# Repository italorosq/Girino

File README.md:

# Girino

Plataforma didática do **LaRA** (Laboratório de Robótica e Automação) para ensino de controle de motores DC. Integra microcontrolador com Wi-Fi, driver de potência L298N e encoder em uma bancada compacta para introdução prática à leitura de sensores, modulação PWM, controle PID e sintonia em malha fechada.

A interface web é embarcada no próprio ESP8266: o aluno conecta na rede do Girino e controla a bancada pelo navegador do celular ou notebook — sem instalar MATLAB, Python ou qualquer software, e sem depender de internet.

## Status do Projeto

| Componente | Status |
|---|---|
| Estrutura do repositório | ✅ Criada |
| Firmware (ESP8266) | ✅ Funcional — PID de velocidade/posição e auto-tune validados em bancada |
| Hardware (PCB — KiCad) | ✅ Projeto KiCad + arquivos de fabricação |
| Mecânico (caixa 3D) | ✅ Modelos STEP (caixa e tampa) |
| Documentação | ✅ |
| Exemplos didáticos | ✅ 5 exemplos |

## Funcionalidades

- **Access Point próprio** (`GIRINO_AP`, `http://192.168.4.1`) — funciona sem roteador e sem internet
- Controle PWM de motor DC via ESP8266 (4 kHz, 8 bits)
- Leitura de encoder incremental (LPD3806-600BM — 600 PPR)
- **Controle PID de velocidade (RPM) e de posição (graus)** em malha fechada
- **Auto-sintonia por relay feedback** (Åström-Hägglund) para velocidade e posição
- **Comparação de métodos de sintonia**: Ziegler-Nichols, Tyreus-Luyben e Cohen-Coon
- Interface web em 3 abas (Velocidade / Posição / Manual), com gráfico de resposta (Chart.js local) e exportação CSV
- **Console serial de comandos** — opera a bancada sem Wi-Fi
- **Auto-calibração do sentido** motor/encoder (fiação invertida corrigida em software)
- Atualização de firmware via OTA (ElegantOTA)
- Design compacto para bancada de laboratório

## Componentes de Hardware

| Componente | Descrição |
|---|---|
| ESP8266 WROOM | Microcontrolador com Wi-Fi (Access Point) |
| LPD3806-600BM | Encoder incremental, 600 pulsos/revolução (saída coletor aberto — pull-up 4,7k para 3,3 V) |
| L298N | Driver de potência do motor DC (ponte H) |
| Motor DC | Motor da bancada |
| Módulo conversão de tensão | Regulador de tensão para alimentação do circuito |

Ligações, pull-ups e montagem passo a passo em [`docs/hardware-assembly.md`](docs/hardware-assembly.md).

## Bancada Medida

| Grandeza | Valor |
|---|---|
| Zona morta do motor | ~60% de duty (abaixo disso o eixo não gira) |
| Região confiável | 70% de duty ≈ 400 RPM |
| Velocidade máxima | 100% ≈ 1950 RPM |
| Precisão de posição | ±2° (o erro residual de ~1–2° é folga mecânica da correia, não do PID) |

## Estrutura do Repositório

```
Girino/
├── firmware/          # Firmware ESP8266 (PlatformIO) + interface web (LittleFS em data/)
├── hardware/          # PCB KiCad, arquivos de fabricação (gerber/NC) e modelos 3D
├── mechanical/        # Peças 3D (em preparação)
├── docs/              # Documentação, pesquisa e infográfico
├── examples/          # Exemplos didáticos passo a passo
├── gallery/           # Fotos e renders do projeto
└── .github/           # Templates e CI/CD
```

## Início Rápido

Veja o guia completo em [`docs/getting-started.md`](docs/getting-started.md).

### Pré-requisitos

- [PlatformIO](https://platformio.org/) (extensão VSCode recomendada)
- Cabo USB para a gravação inicial do ESP8266
- Componentes e montagem: ver [`docs/hardware-assembly.md`](docs/hardware-assembly.md)

### Compilar e Gravar

```bash
cd firmware

# 1. Configurar o Access Point do Girino (SSID, senha e senha do OTA)
cp .env.example .env

# 2. Primeira gravação via USB: firmware + interface web (LittleFS)
pio run -t upload
pio run -t uploadfs

# 3. Conectar no Wi-Fi GIRINO_AP e abrir http://192.168.4.1

# 4. Atualizações seguintes via OTA (PC conectado ao GIRINO_AP)
pio run -t upload --upload-port 192.168.4.1
```

> **Importante:** `pio run -t upload` grava apenas o firmware. A interface web
> vive no LittleFS e é gravada com `pio run -t uploadfs` — obrigatório na
> primeira gravação e sempre que alterar arquivos de `firmware/data/`.

## Documentação

- [Guia de Início Rápido](docs/getting-started.md)
- [Montagem do Hardware](docs/hardware-assembly.md)
- [Guia do Firmware](firmware/README.md) — API REST, pinagem e console serial
- [Atualização OTA](docs/ota-update-guide.md)
- [Análise Comparativa](docs/analise-comparativa.md) — trabalhos relacionados e gap de pesquisa
- [Referências de Pesquisa](docs/referencias-pesquisa.md)
- [Plano PID](docs/plano-pid.md) — métodos de sintonia e arquitetura
- [Resumo UERJ Sem Muros](docs/resumo-uerj-sem-muros.md) — divulgação do projeto

## Exemplos Didáticos

| # | Exemplo | Descrição |
|---|---|---|
| 01 | [Controle Básico de Motor](examples/01-basic-motor-control/) | PWM para controlar velocidade do motor |
| 02 | [Leitura de Encoder](examples/02-encoder-reading/) | Ler pulsos e calcular velocidade |
| 03 | [Controle PID](examples/03-pid-speed-control/) | Malha fechada de velocidade |
| 04 | [OTA Web Update](examples/04-ota-web-update/) | Atualizar firmware via Wi-Fi |
| 05 | [PID Web Test](examples/05-pid-web-test/) | Teste prático de PID com painel web e gráfico |

## Contribuindo

Contribuições são bem-vindas! Veja o guia em [`CONTRIBUTING.md`](CONTRIBUTING.md).

## Licenças

Este projeto utiliza **tripla licença**:

| Tipo | Licença | Arquivo |
|---|---|---|
| Firmware (código) | **GPL-3.0** | [`LICENSE`](LICENSE) |
| Hardware (PCB, esquemático) | **CERN-OHL-S-2.0** | [`LICENSE`](LICENSE) |
| Documentação e imagens | **CC-BY-SA-4.0** | [`LICENSE`](LICENSE) |

## Equipe

Desenvolvido no **LaRA — Laboratório de Robótica e Automação** (UERJ).

## Agradecimentos

- Comunidade open-source ESP8266
- [ElegantOTA](https://github.com/ayushsharma82/ElegantOTA)
- [PlatformIO](https://platformio.org/)

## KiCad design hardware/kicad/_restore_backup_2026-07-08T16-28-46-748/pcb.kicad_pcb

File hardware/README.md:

# Hardware — Girino

Design de PCB para a plataforma didática Girino, desenvolvido em KiCad.

## Estrutura

```
hardware/
├── kicad/          # Projeto KiCad (arquivos-fonte editáveis)
├── gerbers/        # Arquivos Gerber empacotados (.zip) para fabricação
├── bom/            # Bill of Materials (lista de materiais) em CSV
└── schematics/     # PDFs exportados do esquemático
```

## Componentes Principais

| Componente | Qtd | Descrição |
|---|---|---|
| ESP8266 WROOM | 1 | Microcontrolador Wi-Fi |
| LPD3806-600BM | 1 | Encoder incremental 600 PPR |
| Driver MOSFET | 1 | Módulo driver para motor DC |
| Regulador de tensão | 1 | Conversão de tensão para alimentação do circuito |

## Fabricação da PCB

### Gerando Gerbers no KiCad

1. Abra o projeto em `kicad/`
2. Vá em **File → Plot**
3. Selecione as camadas necessárias
4. Gere os arquivos drill
5. Empacote tudo em um `.zip` e salve em `gerbers/`

### Enviando para Fabricação

Arquivos `.zip` em `gerbers/` prontos para enviar a fabricantes como:
- [JLCPCB](https://jlcpcb.com/)
- [PCBWay](https://www.pcbway.com/)
- [Eletrrow](https://www.electrow.com/)

## Convenções

- Nomes de arquivo incluem versão: `gerbers-v1.0.zip`, `bom-v1.0.csv`
- Incluir URL do repositório no silkscreen da PCB
- Arquivos temporários de backup (`.bak`, `*-backups/`) são ignorados pelo git

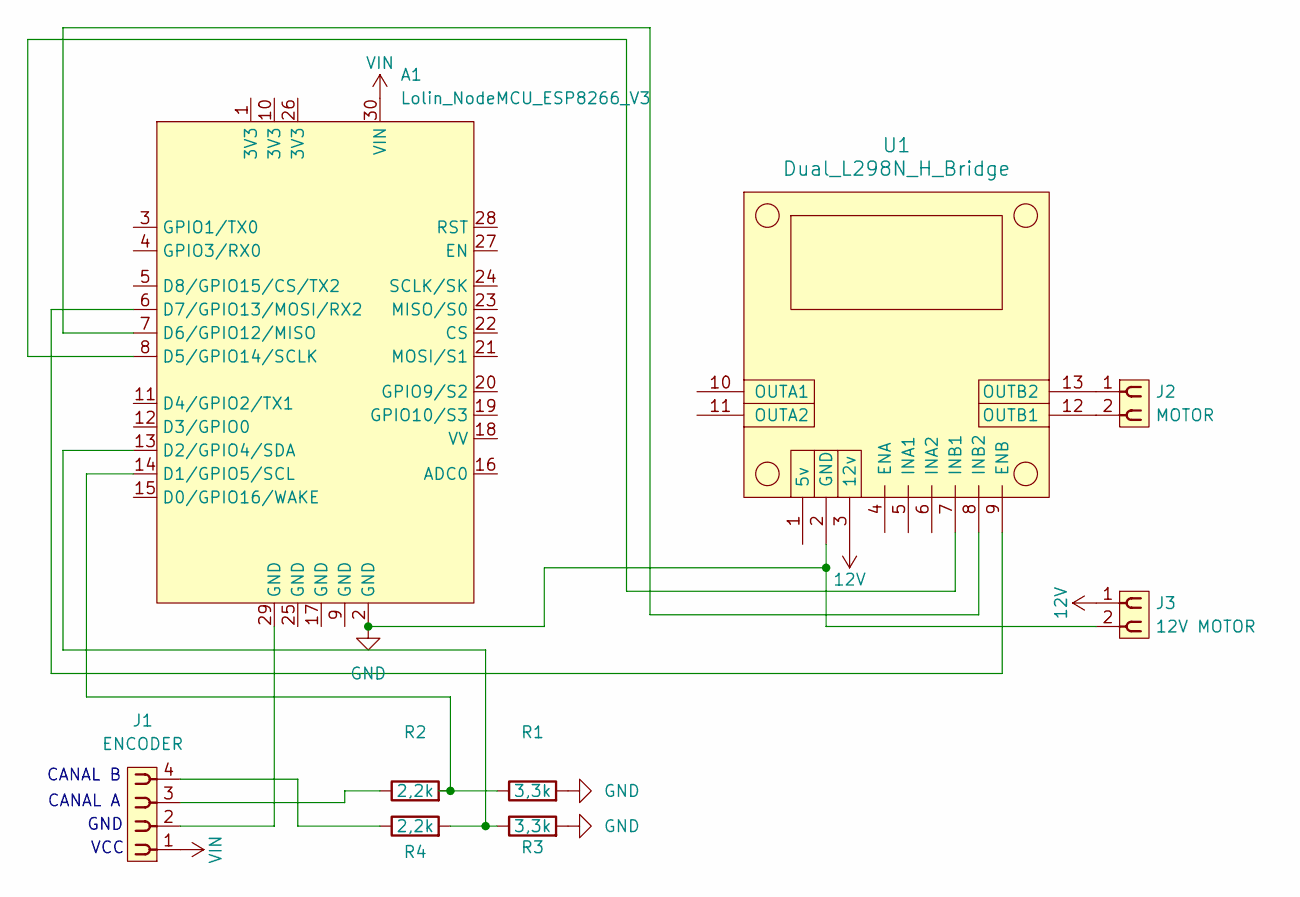
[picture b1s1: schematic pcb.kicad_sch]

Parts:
A1: Lolin_NodeMCU_ESP8266_V3; Lolin_NodeMCU_ESP8266
J1: ENCODER; PinSocket_1x04_P2.54mm_Vertical
J2: MOTOR; PinSocket_1x02_P2.54mm_Vertical
J3: 12V MOTOR; PinSocket_1x02_P2.54mm_Vertical
R1, R3: 3,3k; R_Axial_DIN0207_L6.3mm_D2.5mm_P10.16mm_Horizontal
R2, R4: 2,2k; R_Axial_DIN0207_L6.3mm_D2.5mm_P10.16mm_Horizontal
U1: Dual_L298N_H_Bridge

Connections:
12V: J3.1, U1.3 (12v)
GND: A1.2 (GND), J3.2, R1.2, R3.2, U1.2 (GND)
unnamed: A1.14 (D1/GPIO5/SCL), R1.1, R2.2
unnamed: A1.13 (D2/GPIO4/SDA), R3.1, R4.2
unnamed: A1.8 (D5/GPIO14/SCLK), U1.7 (INB1)
unnamed: A1.7 (D6/GPIO12/MISO), U1.8 (INB2)
unnamed: A1.6 (D7/GPIO13/MOSI/RX2), U1.9 (ENB)
unnamed: A1.29 (GND), J1.2
unnamed: J1.3, R2.1
unnamed: J1.4, R4.1
unnamed: J2.2, U1.12 (OUTB1)
unnamed: J2.1, U1.13 (OUTB2)
VIN: A1.30 (VIN), J1.1

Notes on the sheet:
VCC
GND
CANAL B
CANAL A

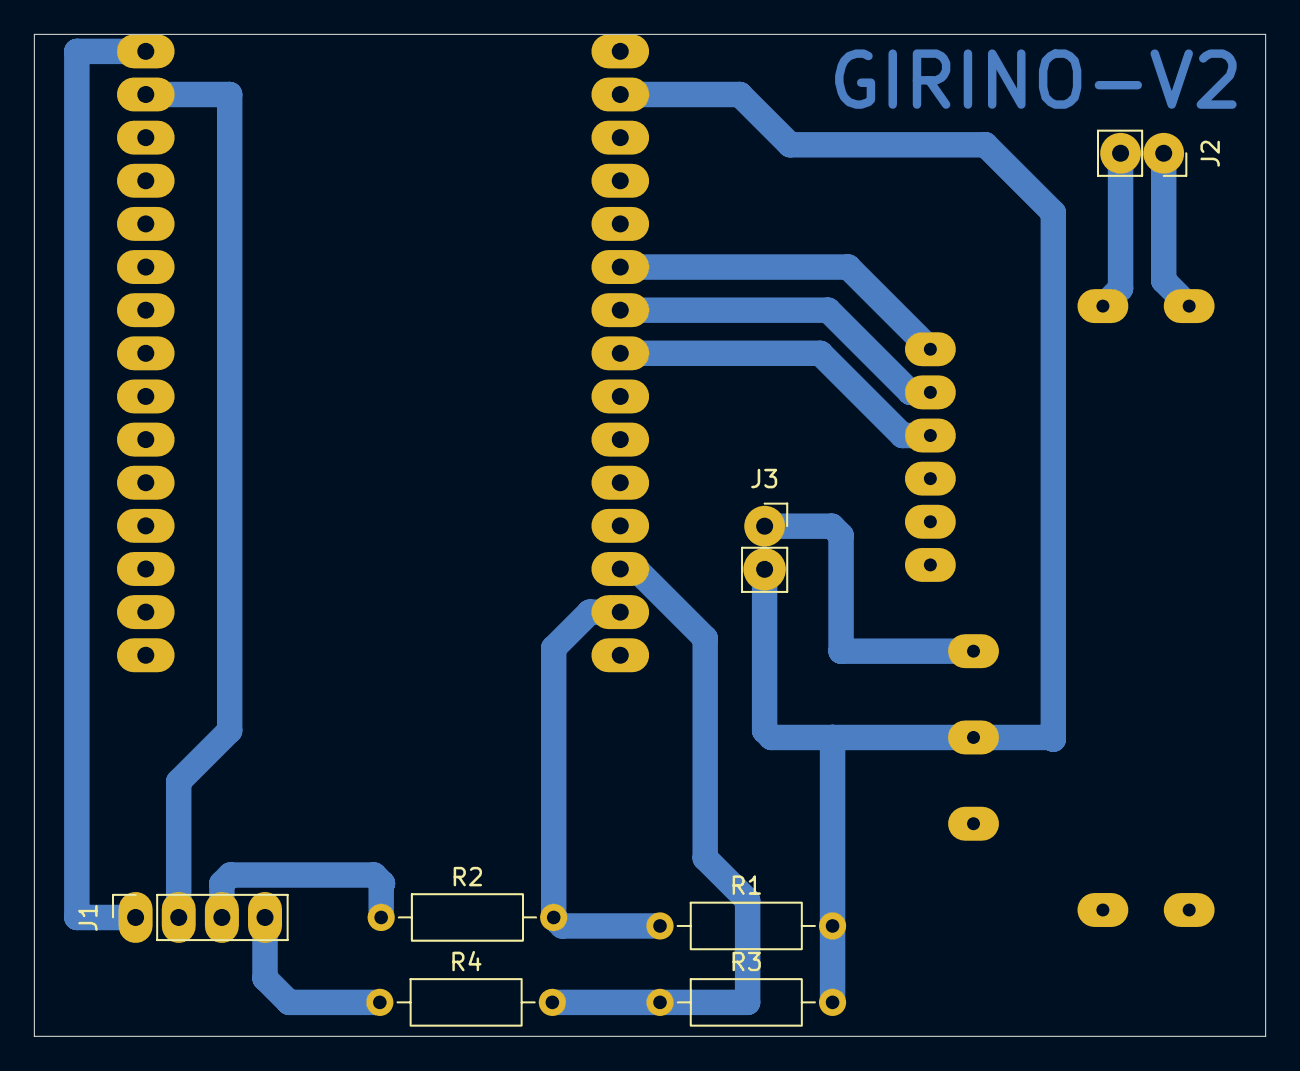
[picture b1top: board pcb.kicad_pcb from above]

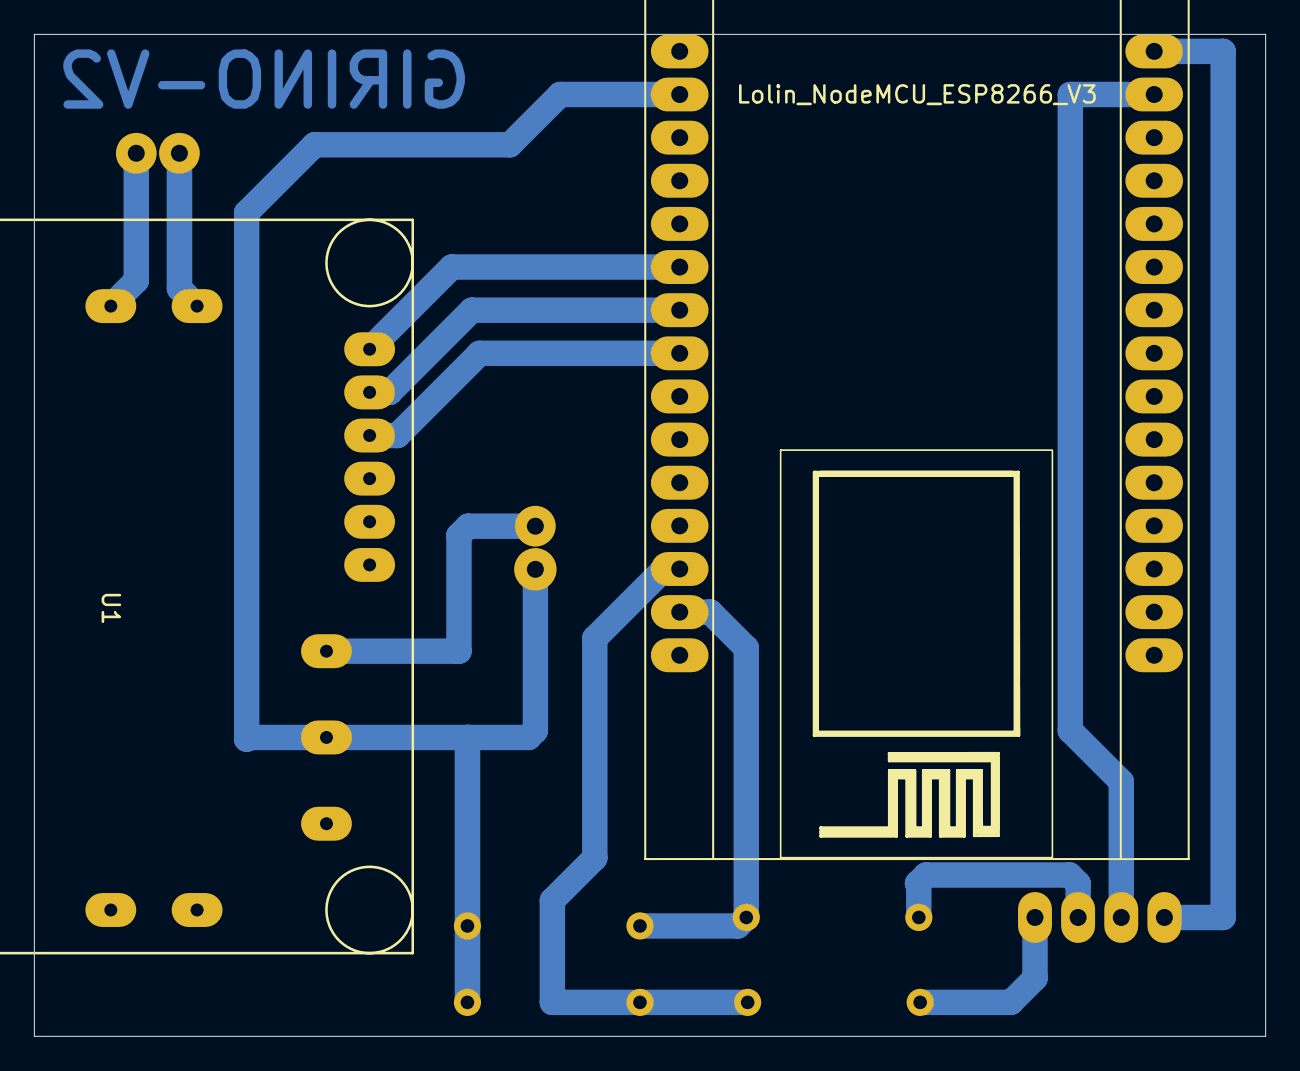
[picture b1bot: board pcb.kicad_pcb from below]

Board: 2 copper layers, 72.5 x 59.0 mm, 9 parts (2 on the bottom side), 13 nets.

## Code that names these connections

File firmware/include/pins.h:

/**
 * pins.h — Definição centralizada dos pinos GPIO do ESP8266
 *
 * Mapeamento de pinos para o hardware Girino.
 * Referência: ESP8266 WROOM (NodeMCU / genérico)
 *
 * GPIO -> Função
 * ──────────────────────────────────
 * D1 (GPIO5)  -> Encoder canal A
 * D2 (GPIO4)  -> Encoder canal B
 * D5 (GPIO14) -> Motor direção (IN3)
 * D6 (GPIO12) -> Motor direção (IN4)
 * D7 (GPIO13) -> Motor PWM (ENB)
 */

#ifndef PINS_H
#define PINS_H

// --- Encoder LPD3806-600BM ---
#define ENCODER_A_PIN    5    // GPIO5  (D1)
#define ENCODER_B_PIN    4    // GPIO4  (D2)

// --- Controle do Motor DC ---
#define MOTOR_PWM_PIN    13   // GPIO13 (D7) - ENB
#define MOTOR_DIR_PIN1   14   // GPIO14 (D5) - IN3
#define MOTOR_DIR_PIN2   12   // GPIO12 (D6) - IN4

// --- LED onboard (debug) ---
#define LED_BUILTIN_PIN  2    // GPIO2 (LED onboard ativo-baixo)

#endif // PINS_H

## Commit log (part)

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2026-05-27 feat: estrutura inicial do projeto Girino
    - Firmware skeleton (PlatformIO + ESP8266): controle PWM, leitura de encoder LPD3806-600BM, OTA via ElegantOTA, interface web com API REST
    - Estrutura de diretórios: firmware/, hardware/, mechanical/, docs/, examples/, gallery/
    - Documentação: getting-started, hardware-assembly, firmware-guide, ota-update-guide
    - Exemplos didáticos: basic-motor-control, encoder-reading, pid-speed-control, ota-web-update
    - Licenças: GPL-3.0 (firmware), CERN-OHL-S-2.0 (hardware), CC-BY-SA-4.0 (docs)
    - Templates: CONTRIBUTING.md, CHANGELOG.md, .gitignore, .env.example
2026-05-27 docs: adicionar plano do módulo PID com auto-tune e comparação de métodos
    - docs/plano-pid.md: planejamento completo do PID
    - 5 métodos de sintonia (ZN, TL, CC, relay feedback, manual)
    - Fluxo de auto-tune via relay feedback (Åström-Hägglund)
    - Arquitetura do firmware (novos arquivos pid.h/cpp, pid_autotune.h/cpp)
    - Novos endpoints API REST para PID
    - Componentes da interface web (gráfico Chart.js)
2026-05-27 feat: adicionar exemplo de teste PID web e alinhar pinagem
2026-05-29 feat: adcionado arquivos da kicad do esquematico e da pcb
2026-06-03 feat : feito os arquivos de pcb e de fabricação via flatcam
2026-06-19 fix : corrige erro de orientação nos arquivos gerber
2026-06-22 feat: interface web com simulador mock para controle de motor
    - Adiciona index.html, style.css e app.js servidos via LittleFS
    - Mobile-first, dark mode, Chart.js para gráfico em tempo real
    - Simulador mock: motor first-order, PID, auto-tune relay feedback
    - Modos: malha aberta, PID manual, auto-tune (ZN/TL/CC)
    - Corrige build_flags duplicados no platformio.ini
    - Remove ESP8266WebServer de lib_deps (já no framework)
2026-06-22 refactor: unificar controles no card de modo, setpoint fixo no PID
    - Move botões Iniciar/Pausar/Parar para header do gráfico (icon-only)
    - Funde mode-panel e open-loop-panel com hr separador
    - Move setpoint para mode-panel (visível só em PID)
    - RPM e Pulsos no chart-footer, dados estáticos no status inferior
    - Adiciona .card-divider, .btn-ctrl, .chart-stat no CSS
2026-06-22 fix: setpoint no gráfico só aparece no modo PID
    - Passa null para setpoint quando não está em modo PID/Auto-Tune
    - spanGaps:false no dataset setpoint (Chart.js ignora nulls)
    - Setpoint no footer mostra '--' quando em malha aberta
2026-06-23 refactor: unificar PID/Auto-Tune no card de modo, limpar gráfico
    - Move PID e Auto-Tune para dentro do mode-panel (uma única section)
    - Remove status-badge 'Parado' do chart-footer
    - Remove _updateRunStatus() e todas as chamadas
    - Adiciona setSetpointVisible() no ChartManager
    - Esconde dataset setpoint + legenda em malha aberta
    - Mostra linha tracejada constante em PID/Auto-Tune
2026-06-23 fix: setpoint aparece no gráfico e footer ao clicar Aplicar
    - _onApplyPid() atualiza statSetpoint.textContent imediatamente
    - Flag setpointConfigured controla exibição do setpoint no gráfico
    - Setpoint no gráfico aparece quando PID/Auto-Tune + configurado
    - Reset setpointConfigured ao mudar para malha aberta

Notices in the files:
README.md:
License: GPL-3.0
License: CERN-OHL-S-2.0
License: CC-BY-SA-4.0
